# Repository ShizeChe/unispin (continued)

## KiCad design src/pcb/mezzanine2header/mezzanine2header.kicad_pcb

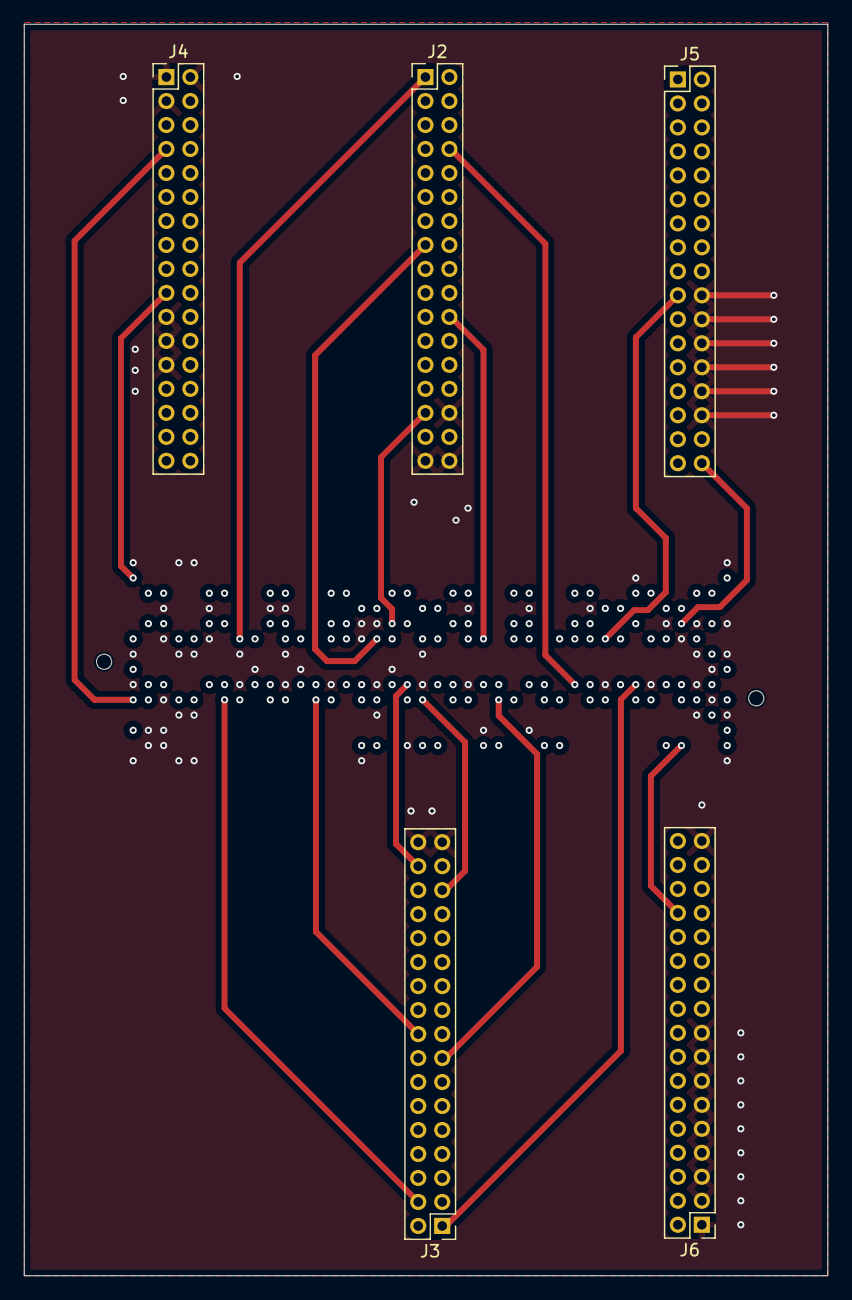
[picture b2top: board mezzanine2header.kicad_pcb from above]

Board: 16 copper layers, 67.0 x 104.3 mm, 6 parts (1 on the bottom side), 144 nets.

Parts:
J1: ASP-184330-01; SAMTEC_ASP-184330-01
J2, J3, J4, J5, J6: Conn_02x17_Odd_Even; PinHeader_2x17_P2.00mm_Vertical

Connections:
C10_LA06_P: J1.C10, J2.5
C11_LA06_N: J1.C11, J2.11
C14_LA10_P: J1.C14, J2.27
C15_LA10_N: J1.C15, J2.23
C18_LA14_P: J1.C18, J2.29
C19_LA14_N: J1.C19, J6.32
C22_LA18_P_CC: J1.C22, J2.28
C23_LA18_N_CC: J1.C23, J2.26
C26_LA27_P: J1.C26, J2.16
C27_LA27_N: J1.C27, J2.14
C30_SCL: J1.C30, J5.27
C31_SDA: J1.C31, J5.29
C34_GA0: J1.C34, J5.14
C37_12P0V: J1.C37, J5.34
C39_3P3V: J1.C39, J6.19
CLK0_M2C_N: J1.H05, J4.13
CLK0_M2C_P: J1.H04, J4.11
CLK1_M2C_N: J1.G03, J4.29
CLK1_M2C_P: J1.G02, J4.27
D1_PG_C2M: J1.D01, J4.17
D8_LA01_P_CC: J1.D08, J2.1
D9_LA01_N_CC: J1.D09, J2.7
D11_LA05_P: J1.D11, J2.13
D12_LA05_N: J1.D12, J2.21
D14_LA09_P: J1.D14, J2.19
D15_LA09_N: J1.D15, J2.17
D17_LA13_P: J1.D17, J2.15
D18_LA13_N: J1.D18, J2.25
D20_LA17_P_CC: J1.D20, J2.31
D21_LA17_N_CC: J1.D21, J6.34
D23_LA23_P: J1.D23, J2.24
D24_LA23_N: J1.D24, J2.22
D26_LA26_P: J1.D26, J2.18
D27_LA26_N: J1.D27, J2.20
D29_TCK: J1.D29, J5.13
D30_TDI: J1.D30, J5.15
D31_TDO: J1.D31, J5.17
D32_3P3VAUX: J1.D32, J5.19
D33_TMS: J1.D33, J5.21
D35_GA1: J1.D35, J5.16
D36_3P3V: J1.D36, J2.32
D38_3P3V: J1.D38, J6.21
DP0_C2M_N: J1.C03, J4.33
DP0_C2M_P: J1.C02, J4.31
DP0_M2C_N: J1.C07, J4.8
DP0_M2C_P: J1.C06, J4.10
DP1_C2M_N: J1.A23, J5.7
DP1_C2M_P: J1.A22, J5.5
DP1_M2C_N: J1.A03, J4.4
DP1_M2C_P: J1.A02, J4.6
DP2_C2M_N: J1.A27, J5.11
DP2_C2M_P: J1.A26, J5.9
DP2_M2C_N: J1.A07, J4.32
DP2_M2C_P: J1.A06, J4.34
DP3_C2M_N: J1.A31, J5.25
DP3_C2M_P: J1.A30, J5.23
DP3_M2C_N: J1.A11, J4.28
DP3_M2C_P: J1.A10, J4.30
DP4_C2M_N: J1.A35, J5.2
DP4_C2M_P: J1.A34, J5.4
DP4_M2C_N: J1.A15, J4.24
DP4_M2C_P: J1.A14, J4.26
DP5_C2M_N: J1.A39, J5.10
DP5_C2M_P: J1.A38, J5.12
DP5_M2C_N: J1.A19, J4.16
DP5_M2C_P: J1.A18, J4.18
DP6_C2M_N: J1.B37, J5.6
DP6_C2M_P: J1.B36, J5.8
DP6_M2C_N: J1.B17, J4.20
DP6_M2C_P: J1.B16, J4.22
DP7_C2M_N: J1.B33, J5.33
DP7_C2M_P: J1.B32, J5.31
E39_VADJ: J1.E39, J5.32
F1_PG_M2C: J1.F01, J4.15
F40_VADJ: J1.F40, J6.23
G6_LA00_P_CC: J1.G06, J2.3
G7_LA00_N_CC: J1.G07, J3.2
G9_LA03_P: J1.G09, J2.9
G10_LA03_N: J1.G10, J3.8
G12_LA08_P: J1.G12, J3.14
G13_LA08_N: J1.G13, J3.16
G15_LA12_P: J1.G15, J3.22
G16_LA12_N: J1.G16, J3.24
G18_LA16_P: J1.G18, J3.30
G19_LA16_N: J1.G19, J3.32
G21_LA20_P: J1.G21, J3.27
G22_LA20_N: J1.G22, J3.25
G24_LA22_P: J1.G24, J3.19
G25_LA22_N: J1.G25, J3.17
G27_LA25_P: J1.G27, J2.12
G28_LA25_N: J1.G28, J2.10
G30_LA29_P: J1.G30, J2.8
G31_LA29_N: J1.G31, J2.6
G33_LA31_P: J1.G33, J3.3
G34_LA31_N: J1.G34, J3.1
G36_LA33_P: J1.G36, J2.4
G37_LA33_N: J1.G37, J2.2
G39_VADJ: J1.G39, J6.25
GBTCLK0_M2C_N: J1.D05, J4.12
GBTCLK0_M2C_P: J1.D04, J4.14
GBTCLK1_M2C_N: J1.B21, J5.3
GBTCLK1_M2C_P: J1.B20, J5.1
GND: J1.B03, J1.B06, J1.B10, J1.B11, J1.B23, J1.B27, J1.B31, J1.C16, J1.C17, J1.C36, J1.C38, J1.C40, J1.D03, J1.D06, J1.D16, J1.D37, J1.E01, J1.E04, J1.E05, J1.E08, J1.E11, J1.E20, J1.E38, J1.E40, J1.F09, J1.F12, J1.F18, J1.F39, J1.G01, J1.G08, J1.G11, J1.G14, J1.G17, J1.G20, J1.G23, J1.G32, J1.G35, J1.G38, J1.H03, J1.H39, J1.J04, J1.J05, J1.J17, J1.J38, J1.J40, J1.K02, J1.K03, J1.K24, J1.K27, J1.L02, J1.L03, J1.L19, J1.M01, J1.M04, J1.M05, J1.M16, J1.M40, J1.Y01, J1.Y04, J1.Y05, J1.Y40, J1.Z34, J2.30, J2.33, J2.34, J3.33, J3.34, J4.1, J4.2, J4.3, J4.21, J4.23, J4.25, J5.20, J5.22, J5.24, J5.26, J5.28, J5.30, J6.1, J6.3, J6.5, J6.7, J6.9, J6.11, J6.13, J6.15, J6.17, J6.33
H1_VREF_A_M2C: J1.H01, J4.7
H2_PRSNT_M2C_L: J1.H02, J4.9
H7_LA02_P: J1.H07, J3.4
H8_LA02_N: J1.H08, J3.6
H10_LA04_P: J1.H10, J3.10
H11_LA04_N: J1.H11, J3.12
H13_LA07_P: J1.H13, J3.18
H14_LA07_N: J1.H14, J3.20
H16_LA11_P: J1.H16, J3.26
H17_LA11_N: J1.H17, J3.28
H19_LA15_P: J1.H19, J3.31
H20_LA15_N: J1.H20, J3.29
H22_LA19_P: J1.H22, J3.23
H23_LA19_N: J1.H23, J3.21
H25_LA21_P: J1.H25, J3.15
H26_LA21_N: J1.H26, J3.13
H28_LA24_P: J1.H28, J3.11
H29_LA24_N: J1.H29, J3.9
H31_LA28_P: J1.H31, J3.7
H32_LA28_N: J1.H32, J3.5
H34_LA30_P: J1.H34, J6.18
H35_LA30_N: J1.H35, J6.20
H37_LA32_P: J1.H37, J6.22
H38_LA32_N: J1.H38, J6.24
H40_VADJ: J1.H40, J6.27
J39_VIO_B_M2C: J1.J39, J6.30
K1_VREF_B_M2C: J1.K01, J4.5
K40_VIO_B_M2C: J1.K40, J6.29
L36_12P0V: J1.L36, J6.26
L37_12P0V: J1.L37, J6.28
L40_12P0V: J1.L40, J6.31
REFCLK_C2M_N: J1.L21, J6.8
REFCLK_C2M_P: J1.L20, J6.6
REFCLK_M2C_N: J1.L25, J6.12
REFCLK_M2C_P: J1.L24, J6.10
SYNC_C2M_N: J1.L17, J6.4
SYNC_C2M_P: J1.L16, J6.2
SYNC_M2C_N: J1.L29, J6.16
SYNC_M2C_P: J1.L28, J6.14
Z1_HSPC_PRSNT_M2C_L: J1.Z01, J4.19
Z40_3P3V: J1.Z40, J5.18

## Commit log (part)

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2025-09-29 placeholder code for rf
2025-09-29 progress on sw
2025-10-11 dc and rf driver
2025-10-13 progress on C code
2025-10-13 launcher
2025-10-13 only li left
2025-10-13 start putting together full system testing c->sv
2025-10-14 reorganized repo structure for rtl+c testing
2025-10-15 swashispin_tb semi-ready
2025-10-15 swashispin_tb can run now
2025-10-15 trace analysis setup
2025-10-15 should just start on pc
2025-10-16 pcb mezzanine2header
2025-10-16 need to debug rf trace
2025-10-20 Create uart_api_dc
2025-10-21 Update uart_api_dc
2025-10-22 24 dc channels + 6 rf channels + 2 dmas can converge
2025-10-22 scripts
2025-10-22 added petalinux build instructions
2025-10-22 dc_dusoatcgher
2025-10-23 dc_select
2025-10-25 need to add register to fix timing
2025-10-28 rtl_base
2025-10-28 adding regiters to meet timing
2025-10-29 dc_dispatcher_test
2025-10-29 timing finaly converged
2025-10-30 0.1ns wns still seems unstable
2025-10-30 registered dc_stream output and rabi_checron.c
2025-10-30 add optional trigger to launch
2025-10-31 test
2025-10-31 fixed rf parameters
2025-10-31 petalinux steps
2025-11-01 fixed rf dac sample format
2025-11-10 formally verified axil slave
2025-11-11 verified axil slave regs on board and deleted designs for mini
2025-11-19 dacboard pcb schematics done
2025-11-24 dacboard routing
2025-11-25 analog side layout
2025-11-25 pcb should reroute
2025-11-26 analog side should be good
2025-11-26 low noise digital finished
2025-11-26 adding more capacitors to analog side
2025-11-26 more capacitors
2025-11-30 finished routing fpga connections
2025-12-01 got rid of all drc errors
2025-12-02 dacboard finished
2025-12-02 board name and date
2025-12-03 fixed a parameter bug in spi master
2025-12-03 got rid of stale sv files
2025-12-03 dacboard au aux ports
2025-12-06 I have a better way to design everything
2025-12-06 redesigned dacboard analog routing
2025-12-07 fixed mosi miso flip in inner section
2025-12-09 start implementing new design idea
2025-12-09 should have a sequencer as a general construct
2025-12-10 major revision ongoing
2025-12-12 rf redesign and reorganizing
2025-12-12 dc redesign in progress
2025-12-12 a bit more
2025-12-13 dc pipeline in progress
2025-12-17 new dc design, needs to task care of ad5791 timing
2025-12-18 fixed some dc_core bugs
2025-12-18 new dc design passed randomized tb
2025-12-23 commit before changes to sw
2025-12-27 assembler working with rtl simulation
2025-12-29 rf assembly halfway done and reorignized things
2025-12-29 rf assembler
2025-12-30 assembler works
2025-12-31 can truly interface with simulator in real time now
2026-01-02 1:1 simulator
2026-01-04 bug fixes
2026-01-04 pushing dacboard asssembly guide
2026-01-04 better dacboard assembly guide
2026-01-06 vivado related stuff
2026-01-06 reorganized and synth
2026-01-06 remove src
2026-01-06 more vivado stuff
2026-01-06 commit before accident
2026-01-07 vivado stuff
2026-01-07 comfortable timing convergence
2026-01-07 button and li asm
2026-01-09 need simulation
2026-01-12 button trigger looks fine in simulation
2026-01-13 good on board
2026-01-14 start li
2026-01-15 adding ctrl regs
2026-01-16 need to simuilate ctrl regs
2026-01-16 fixed compile time errors
2026-01-17 new dc passed randomized test
2026-01-19 old rf tests passed
2026-01-19 nco update verified
2026-01-19 cleaned simulator2
2026-01-19 assembly needs to have ctrl registers
2026-01-20 added control registers to squish
2026-01-20 simulation ready again
2026-01-21 fpga signals can get passed through isolators
2026-01-22 dc rst and clr should default to 1
2026-01-23 wv tcl typo
2026-02-07 board died and some LUTs/regs possibly damaged
2026-02-13 the idea for li
2026-02-17 important deserialize ldac and sync
2026-02-18 li basic design
2026-02-18 push an async fifo
2026-02-18 forgot some li files
2026-02-19 in the process for li
2026-02-20 li core ended up bring quite complicated
2026-02-20 preliminary li verification
2026-02-21 lab local
2026-02-23 big board adc simulator
2026-02-24 home local
2026-02-25 changes to li
2026-02-25 need spi ahead for dc
2026-02-26 dc core idle feature
2026-02-28 asm ldac local
2026-02-28 look into li_sam2insn
2026-03-02 rabi asm
2026-03-02 forgot rabi.asm
2026-03-02 more asm programs
2026-03-03 exchange asm
2026-03-03 some formal properties
2026-03-03 li_save
2026-03-04 bram fifo
2026-03-04 li axi dma
2026-03-05 li save waits verification
2026-03-06 preliminary axi burst master verification
2026-03-09 better verification of li
2026-03-09 added all channels to bd
2026-03-09 some readme
2026-03-11 weird f_past_valid issue in jaspergold
2026-03-11 some formal for async fifo
2026-03-11 single nco_update
2026-03-12 seperated nco update from cores
2026-03-12 adding info to readme
2026-03-12 img folder
2026-03-12 tune readme
2026-03-12 readme render
2026-03-12 try png
2026-03-12 rabi example png
2026-03-12 more readme
2026-03-12 timing good after adding ex
2026-03-13 simulator up again
2026-03-13 better phasor tb
2026-03-13 cordic less than 1 error bound verified
2026-03-14 critical i_k bugfix
2026-03-14 added instant freq/phase shift
2026-03-14 more build info in readme
2026-03-14 title
2026-03-14 README
2026-03-14 minor README fix
2026-03-14 use simualator2 as the default simulator
2026-03-21 ex verification
2026-03-22 ex in assembler
2026-03-23 exchange run
2026-03-24 experiment with bram sequence storage
2026-03-26 bram sequencer
2026-03-28 more bram sequencer
2026-03-31 verifying bram sequencer
2026-03-31 bram sequencer streaming verified
2026-03-31 fixed petalinux steps
2026-03-31 bram sequencer arbitrary next verified
2026-04-01 samll petalinux steps fix
2026-04-02 major changes to assembler
2026-04-02 fixed li and ex load insns
2026-04-03 added status regs
2026-04-04 core status timing good
2026-05-01 updated rtl to report channel status
2026-05-02 squish and simulator setup
2026-05-06 need to fix critical path
2026-05-08 added buffer stage to rf core
2026-05-09 removed button and added squish read
2026-05-11 started new dacboard
2026-05-12 new pcb progress
2026-05-14 finished designing new pcb
2026-05-15 cleared drc
2026-05-15 fixed dac/adcio headers
2026-05-16 double checked new dacboard
2026-06-10 deleted uart functionalities in asm
2026-06-10 reorganized asm
2026-06-17 rtl/tb: add ex_pulse_tb for deterministic exchange.asm ex0 coverage
    - New ex_pulse_tb: 7-insn shortened ex0 (.repeat 4) exercising arm-gated
    idle, lvl pulse amplitude, and (t+4ns) sweep across outer iters.
    Mirrors exp/exchange.asm ex0 structure exactly; only the 19us arm-gate
    and 12us trailing idle are shrunk to 180ns each for sim speed.
    - Loads instructions through the bram_sequencer BRAM-strobe path that
    asm/src/ex.c uses on real hardware (load_insn, load_pc, load_iters,
2026-06-24 prepared verif branch
2026-06-25 reorganized more
2026-06-30 started uvm for dc
